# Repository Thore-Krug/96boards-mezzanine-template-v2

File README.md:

# 96boards-mezzanine-template-v2
Kicad template for creating 96Boards V2 Mezzanines

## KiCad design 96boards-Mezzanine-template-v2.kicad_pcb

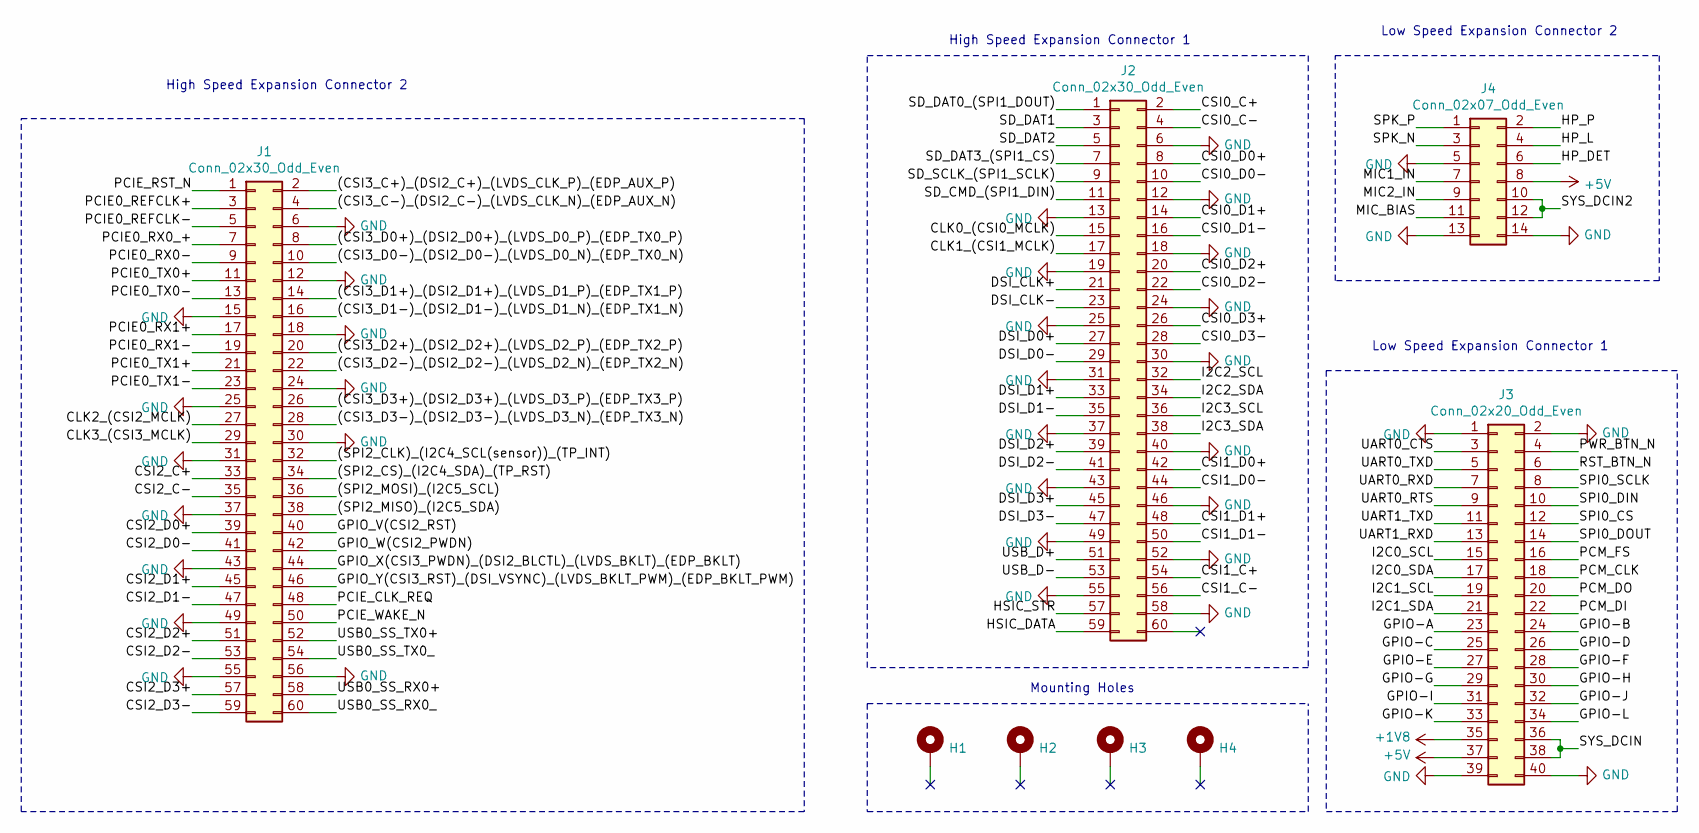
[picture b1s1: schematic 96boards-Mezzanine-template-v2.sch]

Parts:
H1, H2, H3, H4: MountingHole_Pad; MountingHole_2.5mm_Pad
J1, J2: Conn_02x30_Odd_Even; 51790302
J3: Conn_02x20_Odd_Even; PinSocket_2x20_P2.00mm_Vertical
J4: Conn_02x07_Odd_Even; PinSocket_2x07_P2.00mm_Vertical

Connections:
+1V8: J3.35
+5V: J3.37, J4.8
/(CSI3_C+)_(DSI2_C+)_(LVDS_CLK_P)_(EDP_AUX_P): J1.2
/(CSI3_C-)_(DSI2_C-)_(LVDS_CLK_N)_(EDP_AUX_N): J1.4
/(CSI3_D0+)_(DSI2_D0+)_(LVDS_D0_P)_(EDP_TX0_P): J1.8
/(CSI3_D0-)_(DSI2_D0-)_(LVDS_D0_N)_(EDP_TX0_N): J1.10
/(CSI3_D1+)_(DSI2_D1+)_(LVDS_D1_P)_(EDP_TX1_P): J1.14
/(CSI3_D1-)_(DSI2_D1-)_(LVDS_D1_N)_(EDP_TX1_N): J1.16
/(CSI3_D2+)_(DSI2_D2+)_(LVDS_D2_P)_(EDP_TX2_P): J1.20
/(CSI3_D2-)_(DSI2_D2-)_(LVDS_D2_N)_(EDP_TX2_N): J1.22
/(CSI3_D3+)_(DSI2_D3+)_(LVDS_D3_P)_(EDP_TX3_P): J1.26
/(CSI3_D3-)_(DSI2_D3-)_(LVDS_D3_N)_(EDP_TX3_N): J1.28
/(SPI2_CLK)_(I2C4_SCL(sensor))_(TP_INT): J1.32
/(SPI2_CS)_(I2C4_SDA)_(TP_RST): J1.34
/(SPI2_MISO)_(I2C5_SDA): J1.38
/(SPI2_MOSI)_(I2C5_SCL): J1.36
/CLK0_(CSI0_MCLK): J2.15
/CLK1_(CSI1_MCLK): J2.17
/CLK2_(CSI2_MCLK): J1.27
/CLK3_(CSI3_MCLK): J1.29
/CSI0_C+: J2.2
/CSI0_C-: J2.4
/CSI0_D0+: J2.8
/CSI0_D0-: J2.10
/CSI0_D1+: J2.14
/CSI0_D1-: J2.16
/CSI0_D2+: J2.20
/CSI0_D2-: J2.22
/CSI0_D3+: J2.26
/CSI0_D3-: J2.28
/CSI1_C+: J2.54
/CSI1_C-: J2.56
/CSI1_D0+: J2.42
/CSI1_D0-: J2.44
/CSI1_D1+: J2.48
/CSI1_D1-: J2.50
/CSI2_C+: J1.33
/CSI2_C-: J1.35
/CSI2_D0+: J1.39
/CSI2_D0-: J1.41
/CSI2_D1+: J1.45
/CSI2_D1-: J1.47
/CSI2_D2+: J1.51
/CSI2_D2-: J1.53
/CSI2_D3+: J1.57
/CSI2_D3-: J1.59
/DSI_CLK+: J2.21
/DSI_CLK-: J2.23
/DSI_D0+: J2.27
/DSI_D0-: J2.29
/DSI_D1+: J2.33
/DSI_D1-: J2.35
/DSI_D2+: J2.39
/DSI_D2-: J2.41
/DSI_D3+: J2.45
/DSI_D3-: J2.47
/GPIO-A: J3.23
/GPIO-B: J3.24
/GPIO-C: J3.25
/GPIO-D: J3.26
/GPIO-E: J3.27
/GPIO-F: J3.28
/GPIO-G: J3.29
/GPIO-H: J3.30
/GPIO-I: J3.31
/GPIO-J: J3.32
/GPIO-K: J3.33
/GPIO-L: J3.34
/GPIO_V(CSI2_RST): J1.40
/GPIO_W(CSI2_PWDN): J1.42
/GPIO_X(CSI3_PWDN)_(DSI2_BLCTL)_(LVDS_BKLT)_(EDP_BKLT): J1.44
/GPIO_Y(CSI3_RST)_(DSI_VSYNC)_(LVDS_BKLT_PWM)_(EDP_BKLT_PWM): J1.46
/HP_DET: J4.6
/HP_L: J4.4
/HP_P: J4.2
/HSIC_DATA: J2.59
/HSIC_STR: J2.57
/I2C0_SCL: J3.15
/I2C0_SDA: J3.17
/I2C1_SCL: J3.19
/I2C1_SDA: J3.21
/I2C2_SCL: J2.32
/I2C2_SDA: J2.34
/I2C3_SCL: J2.36
/I2C3_SDA: J2.38
/MIC1_IN: J4.7
/MIC2_IN: J4.9
/MIC_BIAS: J4.11
/PCIE0_REFCLK+: J1.3
/PCIE0_REFCLK-: J1.5
/PCIE0_RX0-: J1.9
/PCIE0_RX0_+: J1.7
/PCIE0_RX1+: J1.17
/PCIE0_RX1-: J1.19
/PCIE0_TX0+: J1.11
/PCIE0_TX0-: J1.13
/PCIE0_TX1+: J1.21
/PCIE0_TX1-: J1.23
/PCIE_CLK_REQ: J1.48
/PCIE_RST_N: J1.1
/PCIE_WAKE_N: J1.50
/PCM_CLK: J3.18
/PCM_DI: J3.22
/PCM_DO: J3.20
/PCM_FS: J3.16
/PWR_BTN_N: J3.4
/RST_BTN_N: J3.6
/SD_CMD_(SPI1_DIN): J2.11
/SD_DAT0_(SPI1_DOUT): J2.1
/SD_DAT1: J2.3
/SD_DAT2: J2.5
/SD_DAT3_(SPI1_CS): J2.7
/SD_SCLK_(SPI1_SCLK): J2.9
/SPI0_CS: J3.12
/SPI0_DIN: J3.10
/SPI0_DOUT: J3.14
/SPI0_SCLK: J3.8
/SPK_N: J4.3
/SPK_P: J4.1
/SYS_DCIN: J3.36, J3.38
/SYS_DCIN2: J4.10, J4.12
/UART0_CTS: J3.3
/UART0_RTS: J3.9
/UART0_RXD: J3.7
/UART0_TXD: J3.5
/UART1_RXD: J3.13
/UART1_TXD: J3.11
/USB0_SS_RX0+: J1.58
/USB0_SS_RX0_: J1.60
/USB0_SS_TX0+: J1.52
/USB0_SS_TX0_: J1.54
/USB_D+: J2.51
/USB_D-: J2.53
GND: J1.6, J1.12, J1.15, J1.18, J1.24, J1.25, J1.30, J1.31, J1.37, J1.43, J1.49, J1.55, J1.56, J2.6, J2.12, J2.13, J2.18, J2.19, J2.24, J2.25, J2.30, J2.31, J2.37, J2.40, J2.43, J2.46, J2.49, J2.52, J2.55, J2.58, J3.1, J3.2, J3.39, J3.40, J4.5, J4.13, J4.14

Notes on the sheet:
High Speed Expansion Connector 2
Low Speed Expansion Connector 1
High Speed Expansion Connector 1
Low Speed Expansion Connector 2
Mounting Holes

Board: 2 copper layers, 8 parts (2 on the bottom side), 4 nets, no tracks yet.

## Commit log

2021-04-08 Initial commit
    Bringup of the Mezzanine Template
